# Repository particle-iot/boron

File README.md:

# Boron

<div align=center></div>

### Overview

The Boron LTE is a powerful LTE CAT-M1/NB1 enabled development kit that can act as either a standalone cellular endpoint or LTE enabled gateway for Particle Mesh networks. It is based on the Nordic nRF52840 and has built-in battery charging circuitry so it’s easy to connect a Li-Po and deploy your local network in minutes.

The Boron is great for connecting existing projects to the Particle Device Cloud or as a gateway to connect an entire group of local endpoints where Wi-Fi is missing or unreliable.

### Features

* u-blox SARA R410 LTE modem (Boron LTE)
  * LTE CAT M1/ NB1 module with global hardware support (MVNO support for US only) 
  * 3GPP Release 13 LTE Cat M1 
* u-blox SARA U201 2G/3G modem (Boron 2G/3G)
  * HSPA/GSMqq with global hardware and SIM support 
  * Bands 800/850/900/1900/2100 MHz 
  * 3GPP Release 7 
* Nordic Semiconductor nRF52840 SoC 
  * ARM Cortex-M4F 32-bit processor @ 64MHz 
  * 1MB flash, 256KB RAM 
  * IEEE 802.15.4-2006: 250 Kbps 
  * Bluetooth 5: 2 Mbps, 1 Mbps, 500 Kbps, 125 Kbps 
  * Supports DSP instructions, HW accelerated Floating Point Unit (FPU) calculations 
  * ARM TrustZone CryptoCell-310 Cryptographic and security module 
  * Up to +8 dBm TX power (down to -20 dBm in 4 dB steps) 
  * NFC-A tag
* On-board additional 2MB SPI flash
* 20 mixed signal GPIO (6 x Analog, 8 x PWM), UART, I2C, SPI
* Micro USB 2.0 full speed (12 Mbps)
* Integrated Li-Po charging and battery connector
* JTAG (SWD) Connector
* RGB status LED
* Reset and Mode buttons
* Dual SIM support: Nano 4FF and MFF2
* On-board PCB antenna
* u.FL connector for external antenna
* Meets the Adafruit Feather [specification](https://learn.adafruit.com/adafruit-feather/feather-specification) in dimensions and pinout
* FCC and PTCRB certified
* RoHS compliant (lead-free)

### Structure of this repository:
 - /eagle
     + Contains the schematic and PCB files in the Eagle file format
 - /gerbers
     + Contains the manufacturing gerber files for the board
 - /datasheets
     + Contains the relevant datasheets of the components used on the Boron
 - /pdfs
     + Contains schematic files in PDF 

### Hardware datasheet

The complete datasheet for the Boron is available [here.](https://docs.particle.io/datasheets/cellular/boron-datasheet/
)

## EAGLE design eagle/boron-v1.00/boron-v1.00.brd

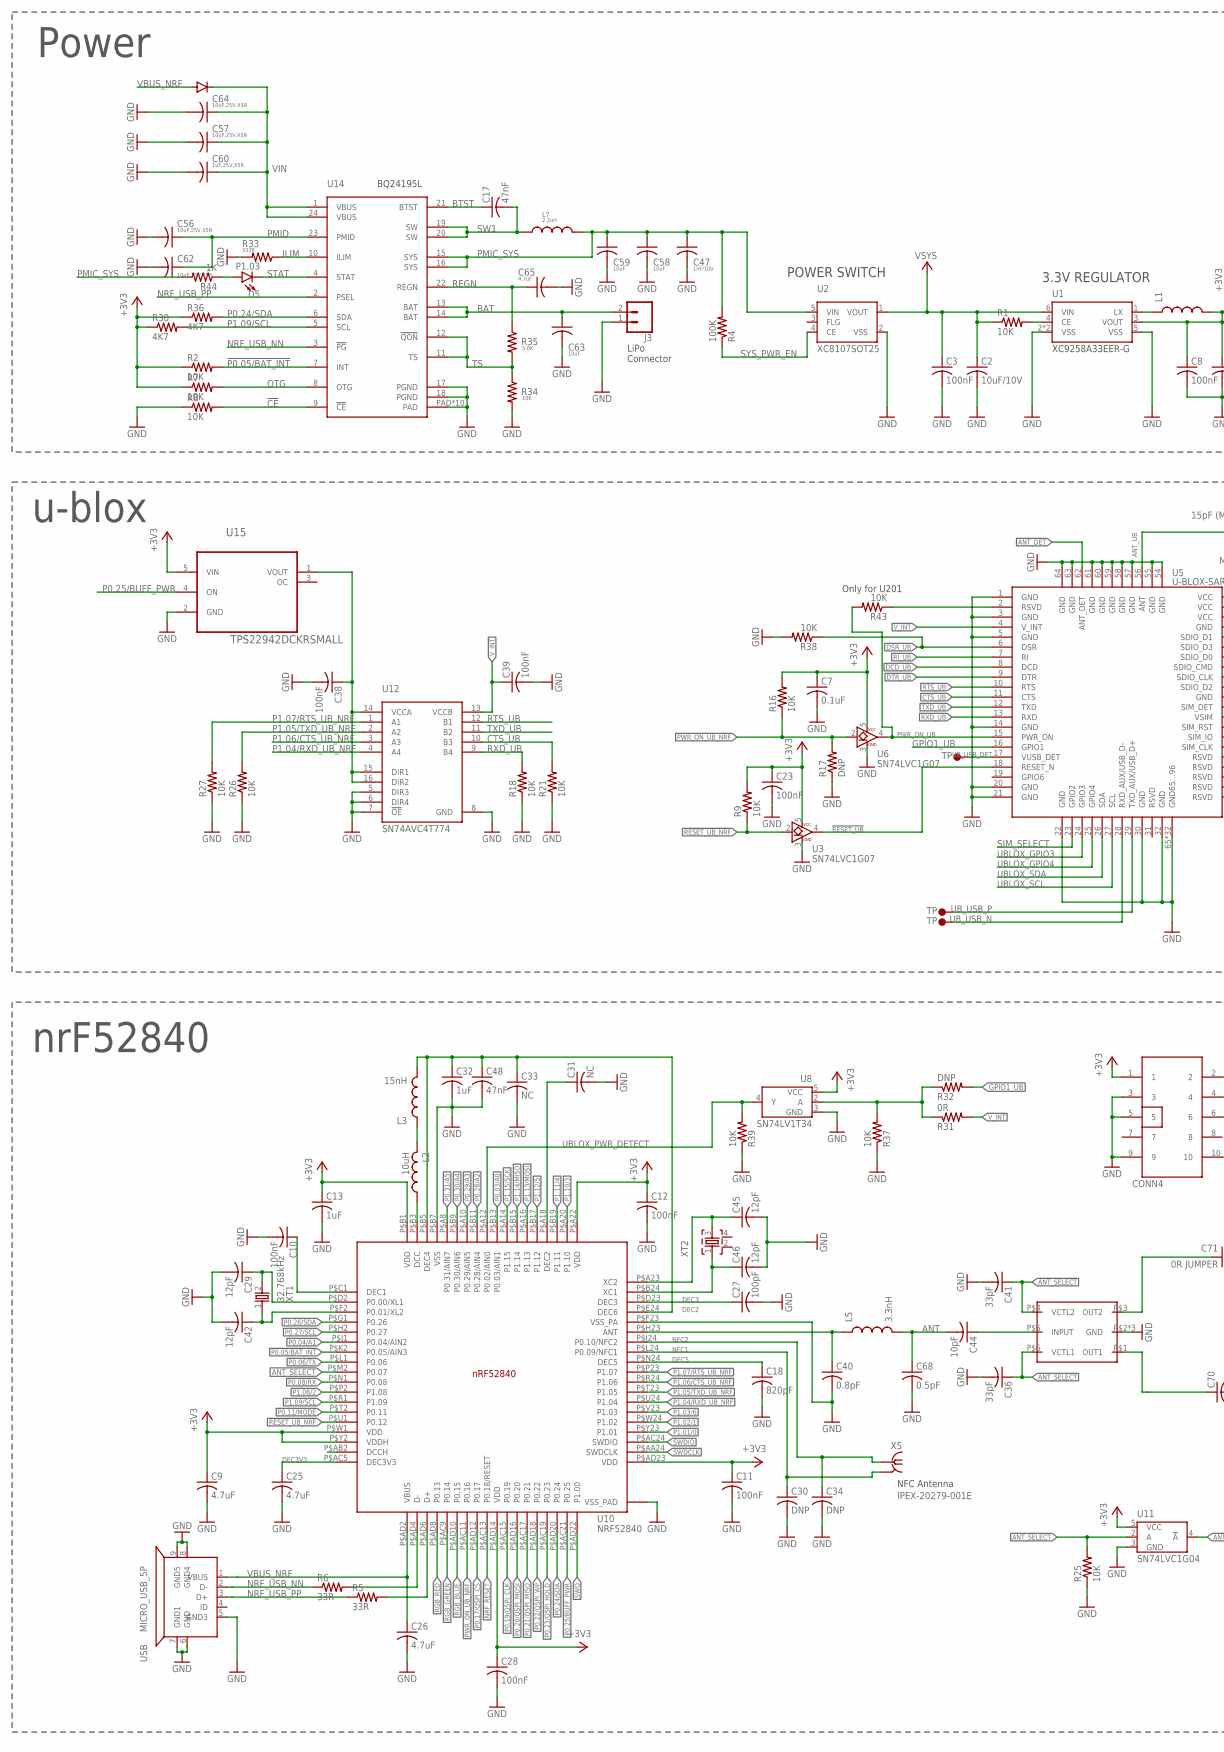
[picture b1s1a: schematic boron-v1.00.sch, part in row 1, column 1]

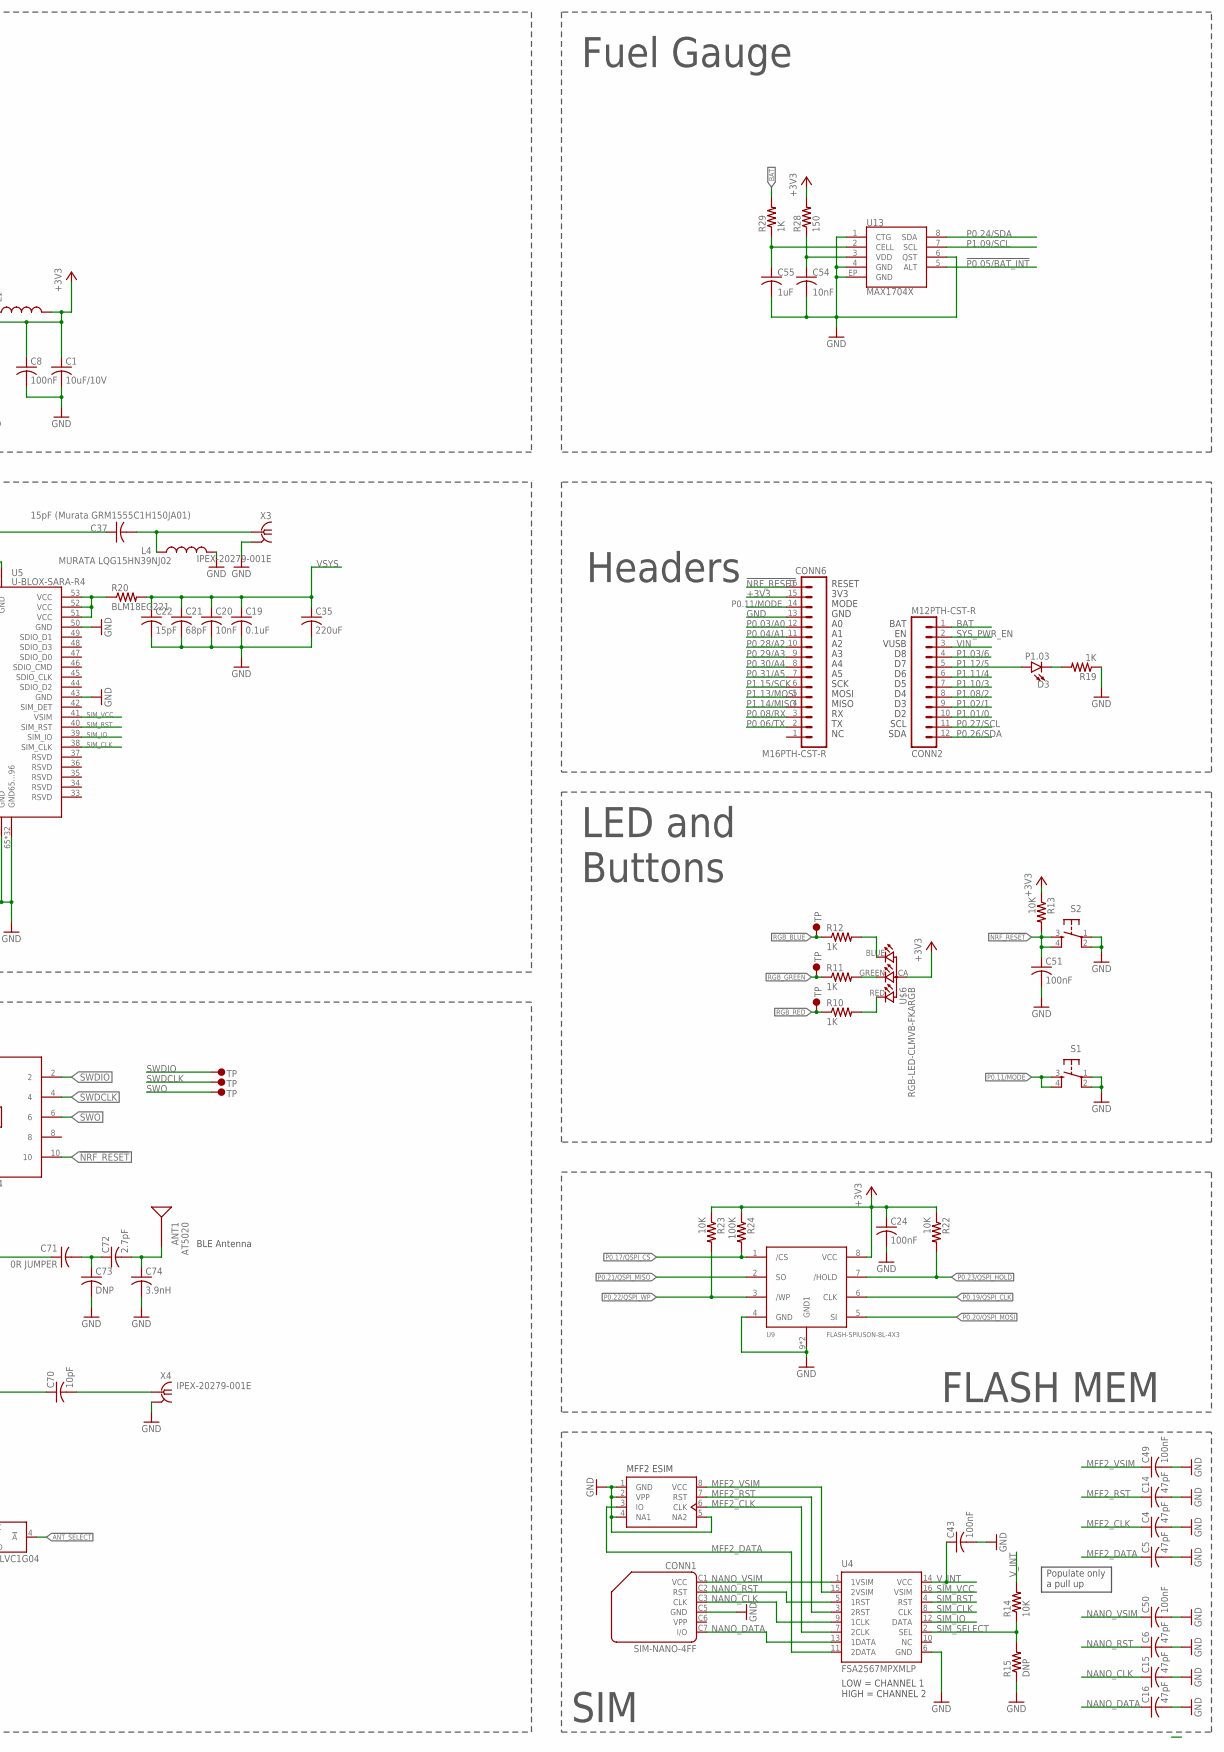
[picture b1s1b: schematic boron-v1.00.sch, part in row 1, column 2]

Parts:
ANT1: AT5020
C1, C2: 10uF/10V; C0603K
C3: 100nF; C0603K
C4, C5, C6, C14, C15, C16: 47pF; C0201_B
C7, C19: 0.1uF; C0402_B
C8, C10, C11, C12, C23, C24, C28, C38, C39, C43, C49, C50, C51: 100nF; C0201_B
C9, C25, C26: 4.7uF; C0402
C13: 1uF; C0402
C17, C48: 47nF; C0201_B
C18: 820pF; C0201_B
C20, C54: 10nF; C0402_B
C21: 68pF; C0402_B
C22: 15pF; C0402_B
C27: 100pF; C0201_B
C29, C42, C45, C46: 12pF; C0201_B
C30, C34, C73: DNP; C0201_B
C31, C33: NC; C0201_B
C32: 1uF; C0402K
C35: 220uF; C1210
C36, C41: 33pF; C0201_B
C37: 15pF (Murata GRM1555C1H150JA01); C0402_B
C40: 0.8pF; C0201_B
C44, C70: 10pF; C0201_B
C47: 1nF/10V; C0402_B
C55: 1uF; C0402_B
C56, C57, C62, C64: 10uF,25V,X5R; C0603_B
C58, C59, C63: 10uF; C0603_B
C60: 1uF,25V,X5R; C0603_B
C65: 4.7uF; C0603_B
C68: 0.5pF; C0201_B
C71: 0R JUMPER; C0201_B
C72: 2.7pF; C0201_B
C74: 3.9nH; C0201_B
CONN1: SIM-NANO-4FF; GCT-SIM8100
CONN2: M12PTH-CST-R; 1X12-CASTELLATED
CONN4: CONN5X2; CONN5X2_1.27
CONN6: M16PTH-CST-R; 1X16-CASTELLATED
D3, D5: P1.03; LED-0603
D4: DIODE_NT; DIODE-DO-220AA_NT(SMP)
J3: CONN_02-JST-2MM-SMT; JST-2-SMD@2
L1: INDUCTOR-SPARKFUNVLS3012ET-4R7M; INDUCTOR-VLS-E
L2: 10uH; RESC0603_L
L3: 15nH; C0402_B
L4: MURATA LQG15HN39NJ02; C0402_B
L5: 3.3nH; C0402_B
L7: 2.2uH; INDUCTOR-4040
R1, R2, R7, R8, R9, R13, R14, R16, R18, R21, R22, R23, R25, R26, R27, R37, R38, R39, R43: 10K; C0201_B
R4, R24: 100K; C0201_B
R5, R6: 33R; C0201_B
R10, R11, R12, R19, R44: 1K; C0201_B
R15, R17, R32: DNP; C0201_B
R20: BLM18EG221; R0603
R28: 150; 0402-RES
R29: 1K; 0402-RES
R30, R36: 4K7; C0201_B
R31: 0R; C0201_B
R33: 333R; R0402_B
R34: 10K; R0402_B
R35: 5.6K; R0402_B
S1, S2: TAC_SWITCHSMD; TACTILE_SWITCH_SMD
U1: XC9258A33EER-G; USP-6C
U2: XC8107SOT25; SOT25
U3, U6: SN74LVC1G07; SC-70-5
U4: FSA2567MPXMLP; MLP16
U5: U-BLOX-SARA-R4; U-BLOX-SARA-U2
U7: ESIMSON8; MFF2
U8: SN74LV1T34; SC70-5
U9: FLASH-SPIUSON-8L-4X3; USON8-3X4
U10: NRF52840; AQFN50P700X700X85_HS-74N
U11: SN74LVC1G04; SC70-5
U12: SN74AVC4T774; UFQFN-16
U13: MAX1704X; TDFN-8
U14: BQ24195L; QFN24
U15: TPS22942DCKRSMALL; SC70-5
U$1, U$4, U$5, U$9, U$10, U$11, U$18, U$19, U$20: TP5; TP30_TOP
U$6: RGB-LED-CLMVB-FKARGB; PLCC4-2MM-RGB
U$7: SKY13351-378LF; MLPD-6-1X1
USB: MICRO_USB_5P; MICRO_USB
X3, X4, X5: IPEX-20279-001E
XT1: 32.768kHz; XTAL_3215_N
XT2: XTAL_32MHZ; BT-XTAL_2016_N

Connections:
!ANT_SELECT: C41.1, U11.4 (!A), U$7.P$4 (VCTL2)
!CE: R8.2, U14.9 (!CE)
!NRF_RESET: C51.1, CONN4.10, CONN6.16, R13.2, S2.3, S2.4, U10.P$AC13 (P0.18/RESET)
!P0.05/BAT_INT: R2.2, U10.P$K2 (P0.05/AIN3), U13.5 (ALT), U14.7 (INT)
!RESET_UB: U3.4 (B), U5.18 (RESET_N)
!RESET_UB_NRF: R9.1, U3.2 (A), U10.P$U1 (P0.12)
+3V3: C1.1, C7.1, C8.1, C9.1, C11.1, C12.1, C13.1, C23.1, C24.1, C28.1, CONN4.1, CONN6.15, L1.P$2 (2), R2.1, R7.1, R9.2, R13.1, R16.2, R22.1, R23.1, R24.1, R28.2, R30.1, R36.1, U1.3 (VOUT), U3.5 (VCC), U6.5 (VCC), U8.5 (VCC), U9.8 (VCC), U10.P$A22 (VDD), U10.P$AD14 (VDD), U10.P$AD23 (VDD), U10.P$B1 (VDD), U10.P$W1 (VDD), U10.P$Y2 (VDDH), U11.5 (VCC), U15.5 (VIN), U$6.CA (1)
ANT: C44.2, C68.1, L5.2
ANT_DET: U5.62 (ANT_DET)
ANT_SELECT: C36.1, R25.2, U10.P$M2 (P0.07), U11.2 (A), U$7.P$6 (VCTL1)
ANT_UB: C37.1, U5.56 (ANT)
BAT: C63.1, CONN2.1, J3.2 (1), R29.2, U14.13 (BAT), U14.14 (BAT)
BTST: C17.1, U14.21 (BTST)
CTS_UB: R21.2, U5.11 (CTS), U12.10 (B3)
DCC: L2.1, U10.P$B3 (DCC)
DCD_UB: U5.8 (DCD)
DEC2: C32.1, C33.1, C48.1, L3.2, U10.P$B5 (DEC4), U10.P$E24 (DEC6)
DEC3: C27.1, U10.P$D23 (DEC3)
DEC3V3: C25.1, U10.P$AC5 (DEC3V3)
DEC5: C18.1, U10.P$N24 (DEC5)
DSR_UB: R38.1, U5.6 (DSR)
DTR_UB: U5.9 (DTR)
GND: C1.2, C2.2, C3.2, C4.2, C5.2, C6.2, C7.2, C8.2, C9.2, C10.2, C11.2, C12.2, C13.2, C14.2, C15.2, C16.2, C18.2, C19.2, C20.2, C21.2, C22.2, C23.2, C24.2, C25.2, C26.2, C27.2, C28.2, C29.2, C30.2, C31.2, C32.2, C33.2, C34.2, C35.2, C36.2, C38.2, C39.2, C40.2, C41.2, C42.2, C43.2, C45.2, C46.2, C47.2, C48.2, C49.2, C50.2, C51.2, C54.2, C55.2, C56.2, C57.2, C58.2, C59.2, C60.2, C62.2, C63.2, C64.2, C65.2, C68.2, C73.2, C74.2, CONN1.C5 (GND), CONN4.3, CONN4.5, CONN4.9, CONN6.13, J3.1 (2), L4.2, R8.1, R15.1, R17.1, R18.1, R19.1, R21.1, R25.1, R26.1, R27.1, R33.2, R34.2, R37.1, R38.2, R39.1, S1.1, S1.2, S2.1, S2.2, U1.2 (VSS), U1.5 (VSS), U1.P$1 (VSS), U2.2 (VSS), U3.3 (GND), U4.6 (GND), U5.1 (GND), U5.3 (GND), U5.5 (GND), U5.14 (GND), U5.20 (GND), U5.21 (GND), U5.22 (GND), U5.30 (GND), U5.32 (GND), U5.43 (GND), U5.50 (GND), U5.54 (GND), U5.55 (GND), U5.57 (GND), U5.58 (GND), U5.59 (GND), U5.60 (GND), U5.61 (GND), U5.63 (GND), U5.64 (GND), U5.65 (GND65...96), U5.66 (GND65...96), U5.67 (GND65...96), U5.68 (GND65...96), U5.69 (GND65...96), U5.70 (GND65...96), U5.71 (GND65...96), U5.72 (GND65...96), U5.73 (GND65...96), U5.74 (GND65...96), U5.75 (GND65...96), U5.76 (GND65...96), U5.77 (GND65...96), U5.78 (GND65...96), U5.79 (GND65...96), U5.80 (GND65...96), U5.81 (GND65...96), U5.82 (GND65...96), U5.83 (GND65...96), U5.84 (GND65...96), U5.85 (GND65...96), U5.86 (GND65...96), U5.87 (GND65...96), U5.88 (GND65...96), U5.89 (GND65...96), U5.90 (GND65...96), U5.91 (GND65...96), U5.92 (GND65...96), U5.93 (GND65...96), U5.94 (GND65...96), U5.95 (GND65...96), U5.96 (GND65...96), U6.3 (GND), U7.1 (GND), U7.2 (VPP), U7.4 (NA1), U7.5 (NA2), U8.3 (GND), U9.4 (GND), U9.9 (GND1), U9.10 (GND1), U10.P$74 (VSS_PAD), U10.P$75 (VSS_PAD), U10.P$76 (VSS_PAD), U10.P$77 (VSS_PAD), U10.P$78 (VSS_PAD), U10.P$79 (VSS_PAD), U10.P$80 (VSS_PAD), U10.P$81 (VSS_PAD), U10.P$82 (VSS_PAD), U10.P$83 (VSS_PAD), U10.P$B7 (VSS), U10.P$F23 (VSS_PA), U11.3 (GND), U12.5 (DIR3), U12.6 (DIR4), U12.7 (!OE), U12.8 (GND), U13.1 (CTG), U13.4 (GND), U13.6 (QST), U13.EP (GND), U14.17 (PGND), U14.18 (PGND), U14.PAD, U14.PAD@1 (PAD), U14.PAD@2 (PAD), U14.PAD@3 (PAD), U14.PAD@4 (PAD), U14.PAD@5 (PAD), U14.PAD@6 (PAD), U14.PAD@7 (PAD), U14.PAD@8 (PAD), U14.PAD@9 (PAD), U15.2 (GND), U$7.P$2 (GND), U$7.P$7 (GND), U$7.P$8 (GND), USB.5 (GND3), USB.6 (GND), USB.7 (GND1), USB.8 (GND4), USB.9 (GND5), X3.2@1 (GND), X3.2@2 (GND), X4.2@1 (GND), X4.2@2 (GND)
GPIO1_UB: R32.2, U5.16 (GPIO1)
ILIM: R33.1, U14.10 (ILIM)
MFF2_CLK: C4.1, U4.7 (2CLK), U7.6 (CLK)
MFF2_DATA: C5.1, U4.11 (2DATA), U7.3 (IO)
MFF2_RST: C14.1, U4.3 (2RST), U7.7 (RST)
MFF2_VSIM: C49.1, U4.15 (2VSIM), U7.8 (VCC)
unnamed: C37.2, L4.1, X3.1
unnamed: C44.1, U$7.P$5 (INPUT)
unnamed: R12.2, U$6.BLUE (2)
unnamed: C38.1, U12.14 (VCCA), U12.15 (DIR1), U12.16 (DIR2), U15.1 (VOUT)
unnamed: R11.2, U$6.GREEN (3)
unnamed: R20.1, U5.51 (VCC), U5.52 (VCC), U5.53 (VCC)
unnamed: R10.2, U$6.RED (4)
unnamed: C70.1, U$7.P$1 (OUT1)
unnamed: C40.1, L5.1, U10.P$H23 (ANT)
unnamed: R31.1, R32.1, R37.2, U8.2 (A)
unnamed: D5.A, R44.1
unnamed: R1.2, U1.4 (CE)
unnamed: D3.C, R19.2
unnamed: L1.P$1 (1), U1.1 (LX)
unnamed: C31.1, U10.P$A18 (DEC2)
unnamed: C71.1, U$7.P$3 (OUT2)
unnamed: C70.2, X4.1
unnamed: C71.2, C72.1, C73.1
unnamed: R43.1, U5.2 (RSVD)
unnamed: ANT1.1, C72.2, C74.1
unnamed: C54.1, R28.1, U13.3 (VDD)
unnamed: C55.1, R29.1, U13.2 (CELL)
unnamed: C10.1, U10.P$C1 (DEC1)
unnamed: L2.2, L3.1
NANO_CLK: C15.1, CONN1.C3 (CLK), U4.9 (1CLK)
NANO_DATA: C16.1, CONN1.C7 (I/O), U4.13 (1DATA)
NANO_RST: C6.1, CONN1.C2 (RST), U4.5 (1RST)
NANO_VSIM: C50.1, CONN1.C1 (VCC), U4.1 (1VSIM)
NFC1: C30.1, U10.P$L24 (P0.09/NFC1), X5.2@1 (GND), X5.2@2 (GND)
NFC2: C34.1, U10.P$J24 (P0.10/NFC2), X5.1
NRF_USB_N: R6.2, U10.P$AD4 (D-)
NRF_USB_NN: R6.1, U14.3 (!PG), USB.2 (D-)
NRF_USB_P: R5.2, U10.P$AD6 (D+)
NRF_USB_PP: R5.1, U14.2 (PSEL), USB.3 (D+)
OTG: R7.2, U14.8 (OTG)
P0.03/A0: CONN6.12, U10.P$B13 (P0.03/AIN1)
P0.04/A1: CONN6.11, U10.P$J1 (P0.04/AIN2)
P0.06/TX: CONN6.2, U10.P$L1 (P0.06)
P0.08/RX: CONN6.3, U10.P$N1 (P0.08)
P0.11/MODE: CONN6.14, S1.3, S1.4, U10.P$T2 (P0.11)
P0.17/QSPI_CS: R24.2, U9.1 (/CS), U10.P$AD12 (P0.17)
P0.19/QSPI_CLK: U9.6 (CLK), U10.P$AC15 (P0.19)
P0.20/QSPI_MOSI: U9.5 (SI), U10.P$AD16 (P0.20)
P0.21/QSPI_MISO: U9.2 (SO), U10.P$AC17 (P0.21)
P0.22/QSPI_WP: R23.2, U9.3 (/WP), U10.P$AD18 (P0.22)
P0.23/QSPI_HOLD: R22.2, U9.7 (/HOLD), U10.P$AC19 (P0.23)
P0.24/SDA: R36.2, U10.P$AD20 (P0.24), U13.8 (SDA), U14.6 (SDA)
P0.25/BUFF_PWR: U10.P$AC21 (P0.25), U15.4 (ON)
P0.26/SDA: CONN2.12, U10.P$G1 (P0.26)
P0.27/SCL: CONN2.11, U10.P$H2 (P0.27)
P0.28/A2: CONN6.10, U10.P$B11 (P0.28/AIN4)
P0.29/A3: CONN6.9, U10.P$A10 (P0.29/AIN5)
P0.30/A4: CONN6.8, U10.P$B9 (P0.30/AIN6)
P0.31/A5: CONN6.7, U10.P$A8 (P0.31/AIN7)
P1.01/0: CONN2.10, U10.P$Y23 (P1.01)
P1.02/1: CONN2.9, U10.P$W24 (P1.02)
P1.03/6: CONN2.4, U10.P$V23 (P1.03)
P1.04/RXD_UB_NRF: U10.P$U24 (P1.04), U12.4 (A4)
P1.05/TXD_UB_NRF: R26.2, U10.P$T23 (P1.05), U12.2 (A2)
P1.06/CTS_UB_NRF: U10.P$R24 (P1.06), U12.3 (A3)
P1.07/RTS_UB_NRF: R27.2, U10.P$P23 (P1.07), U12.1 (A1)
P1.08/2: CONN2.8, U10.P$P2 (P1.08)
P1.09/SCL: R30.2, U10.P$R1 (P1.09), U13.7 (SCL), U14.5 (SCL)
P1.10/3: CONN2.7, U10.P$A20 (P1.10)
P1.11/4: CONN2.6, U10.P$B19 (P1.11)
P1.12/5: CONN2.5, D3.A, U10.P$B17 (P1.12)
P1.13/MOSI: CONN6.5, U10.P$A16 (P1.13)
P1.14/MISO: CONN6.4, U10.P$B15 (P1.14)
P1.15/SCK: CONN6.6, U10.P$A14 (P1.15)
PMIC_SYS: C47.1, C58.1, C59.1, L7.P$2 (2), R4.2, R44.2, U2.5 (VIN), U14.15 (SYS), U14.16 (SYS)
PMID: C56.1, C62.1, U14.23 (PMID)
PWR_ON_UB: R43.2, U5.15 (PWR_ON), U6.4 (B)
PWR_ON_UB_NRF: R16.1, R17.2, U6.2 (A), U10.P$AC11 (P0.16)
REGN: C65.1, R35.1, U14.22 (REGN)
RGB_BLUE: R12.1, U10.P$AD10 (P0.15), U$11.P$1
RGB_GREEN: R11.1, U10.P$AC9 (P0.14), U$10.P$1
RGB_RED: R10.1, U10.P$AD8 (P0.13), U$9.P$1
RI_UB: U5.7 (RI)
RTS_UB: U5.10 (RTS), U12.12 (B1)
RXD_UB: R18.2, U5.13 (RXD), U12.9 (B4)
SIM_CLK: U4.8 (CLK), U5.38 (SIM_CLK)
SIM_IO: U4.12 (DATA), U5.39 (SIM_IO)
SIM_RST: U4.4 (RST), U5.40 (SIM_RST)
SIM_SELECT: R14.1, R15.2, U4.2 (SEL), U5.23 (GPIO2)
SIM_VCC: U4.16 (VSIM), U5.41 (VSIM)
STAT: D5.C, U14.4 (STAT)
SW1: C17.2, L7.P$1 (1), U14.19 (SW), U14.20 (SW)
SWDCLK: CONN4.4, U10.P$AA24 (SWDCLK), U$4.P$1
SWDIO: CONN4.2, U10.P$AC24 (SWDIO), U$1.P$1
SWO: CONN4.6, U10.P$AD22 (P1.00), U$5.P$1
SYS_PWR_EN: CONN2.2, R4.1, U2.4 (CE)
TS: R34.1, R35.2, U14.11 (TS), U14.12 (!QON)
TXD_UB: U5.12 (TXD), U12.11 (B2)
UBLOX_GPIO3: U5.24 (GPIO3)
UBLOX_GPIO4: U5.25 (GPIO4)
UBLOX_PWR_DETECT: R39.2, U8.4 (Y), U10.P$A12 (P0.02/AIN0)
UBLOX_SCL: U5.27 (SCL)
UBLOX_SDA: U5.26 (SDA)
UB_USB_DET: U5.17 (VUSB_DET), U$20.P$1
UB_USB_N: U5.28 (RXD_AUX/USB_D-), U$19.P$1
UB_USB_P: U5.29 (TXD_AUX/USB_D+), U$18.P$1
VBUS_NRF: C26.1, D4.ANODE, U10.P$AD2 (VBUS), USB.1 (VBUS)
VIN: C57.1, C60.1, C64.1, CONN2.3, D4.CATHODE, U14.1 (VBUS), U14.24 (VBUS)
VSYS: C2.1, C3.1, C19.1, C20.1, C21.1, C22.1, C35.1, R1.1, R20.2, U1.6 (VIN), U2.1 (VOUT)
V_INT: C39.1, C43.1, R14.2, R31.2, U4.14 (VCC), U5.4 (V_INT), U12.13 (VCCB)
XC1: C46.1, U10.P$B24 (XC1), XT2.1
XC2: C45.1, U10.P$A23 (XC2), XT2.3
XL1: C29.1, U10.P$D2 (P0.00/XL1), XT1.2
XL2: C42.1, U10.P$F2 (P0.01/XL2), XT1.1

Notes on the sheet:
MISO
MOSI
SCK
GND
MODE
3V3
RESET
SDA
SCL
VUSB
BAT
NFC Antenna
BLE Antenna
MFF2 ESIM
Populate only a pull up
3.3V REGULATOR
LiPo Connector
nrF52840
u-blox
Power
Headers
LED and Buttons
FLASH MEM
SIM
Fuel Gauge
Only for U201
LOW = CHANNEL 1 HIGH = CHANNEL 2
POWER SWITCH

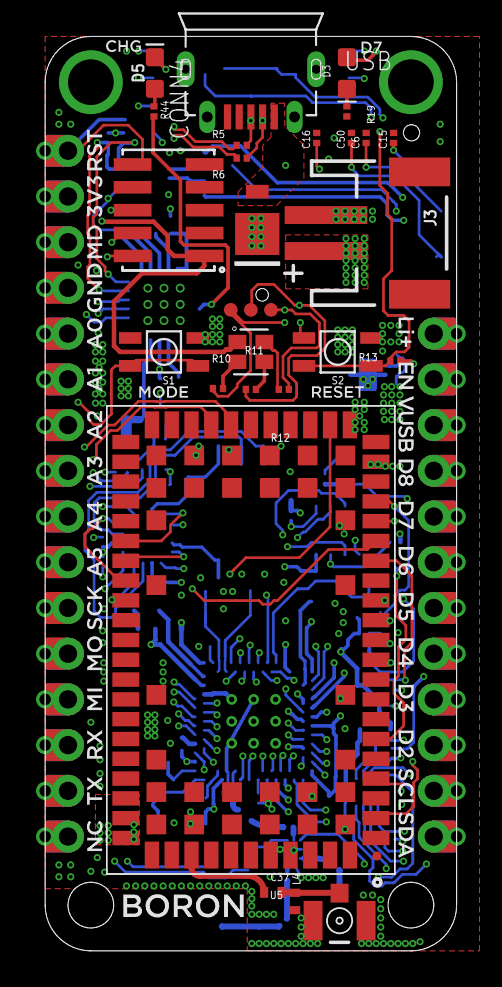
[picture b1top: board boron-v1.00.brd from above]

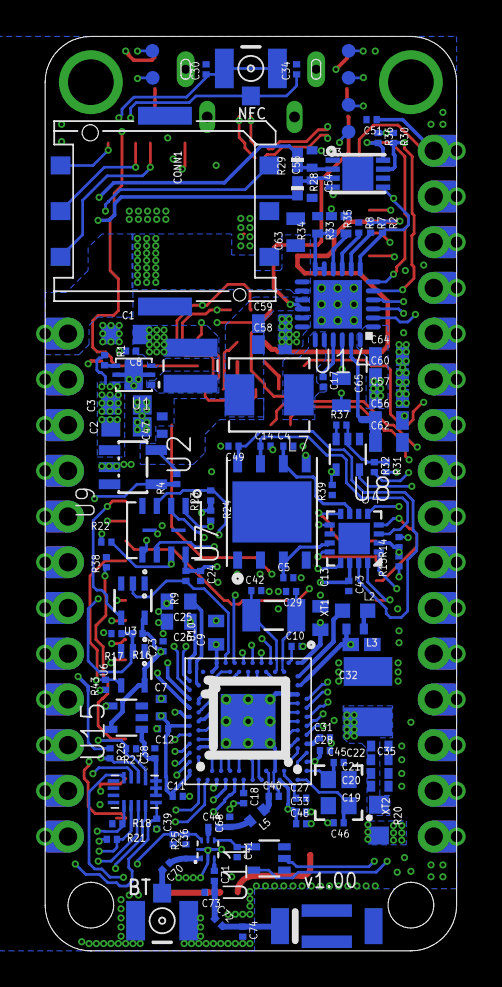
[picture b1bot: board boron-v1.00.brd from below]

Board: 8 copper layers, 22.9 x 50.8 mm, 157 parts (129 on the bottom side), 130 nets.

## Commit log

2018-10-03 added design files
2018-10-30 updated readme and added files
2018-10-30 Fix bullets. Silly GFM.
2018-12-19 Add schematic pdf
2019-03-04 Include MX25L3233F SPI flash datasheet

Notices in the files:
parts and their libraries:
SparkFun-Connectors: Licensing: Creative Commons ShareAlike 4.0 International - https://creativecommons.org/licenses/by-sa/4.0
